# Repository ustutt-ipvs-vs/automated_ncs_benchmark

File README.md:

# Automated NCS Benchmark Setup
This repository contains the source code, hardware schematics, 3D printing files, and documentation of the open source benchmark setup described in the paper "Combining Dynamic Deterministic Latency Bounds and Networked Control Systems".

The paper can be found here: https://doi.org/10.1109/IPCCC59868.2024.10850021

The video below shows a demo of an automated evaluation with 15 configurations and re-swing-ups between each configuration.

[Demo Video](https://github.com/ustutt-ipvs-vs/automated_ncs_benchmark/assets/69897594/da2cac4a-8f67-4f81-817d-bd36dadb8c46)

## Overview
This repository is structured as follows:

- `sender-receiver-linux`: Software components for the sender side and receiver side computers
- `sender-receiver-teensy`: Sender and receiver scripts for the Teensy microcontrollers
- `network-config`: Bash scripts to configure the software switch and the endpoints
    - `scheduling-switch-config`: Scripts to configure the Qdisc and queue sizes at the software switch
- `control-approaches-design`: Files containing calculations for the parameters of the various control approaches for the inverted pendulum.
- `PCB-Design`: Design files of the sender and receiver PCB (KiCad)
- `3d-printable-parts`: Design files of the 3D-printed parts that were used for the construction of the inverted pendulum.
- `photos`: Photos of the inverted pendulum

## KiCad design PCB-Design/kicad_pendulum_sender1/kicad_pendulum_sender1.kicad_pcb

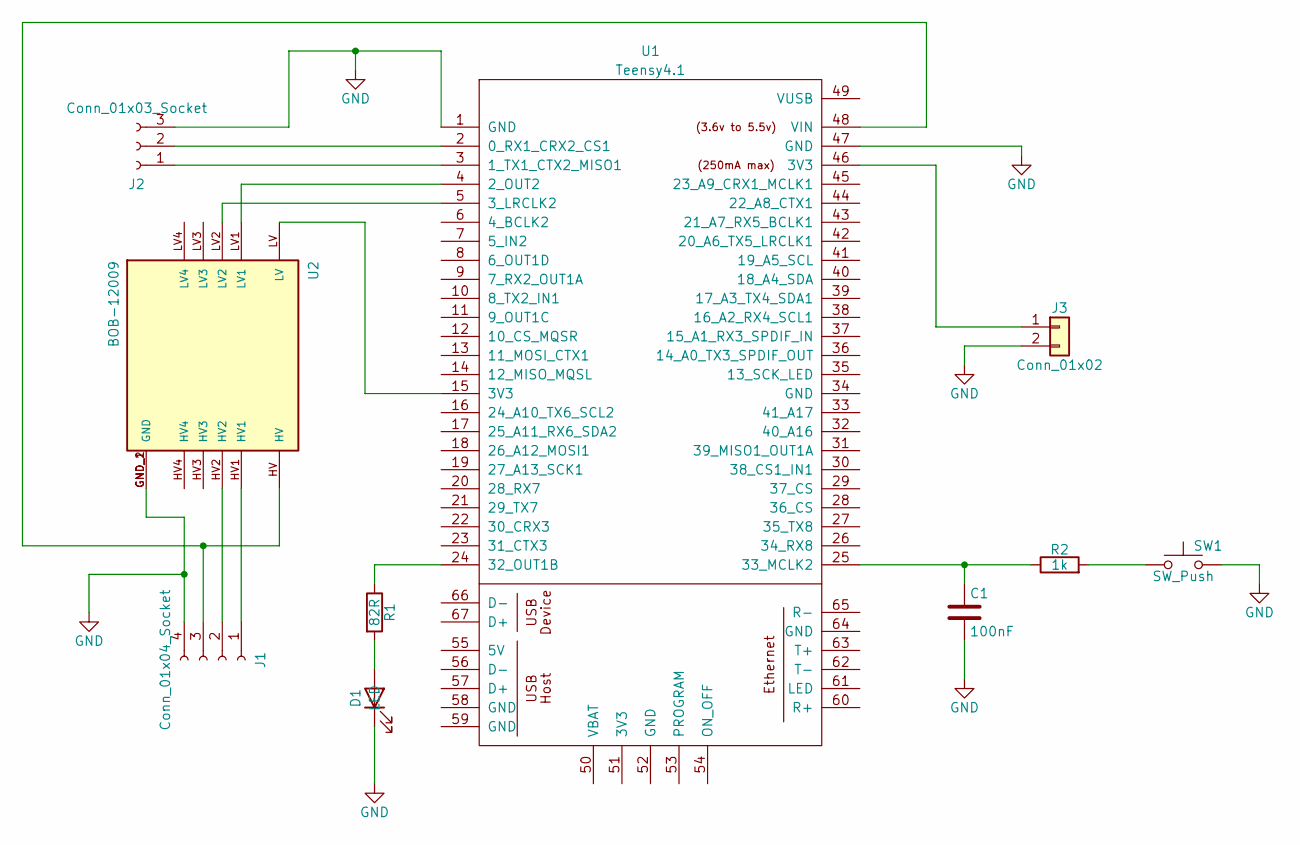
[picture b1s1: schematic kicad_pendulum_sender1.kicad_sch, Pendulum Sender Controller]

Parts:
C1: 100nF; C_Disc_D4.7mm_W2.5mm_P5.00mm
D1: LED; LED_D3.0mm
J1: Conn_01x04_Socket; TerminalBlock_bornier-4_P5.08mm
J2: Conn_01x03_Socket; TerminalBlock_bornier-3_P5.08mm
J3: Conn_01x02; TerminalBlock_bornier-2_P5.08mm
R1: 82R; R_Axial_DIN0207_L6.3mm_D2.5mm_P10.16mm_Horizontal
R2: 1k; R_Axial_DIN0207_L6.3mm_D2.5mm_P10.16mm_Horizontal
SW1: SW_Push; SW_PUSH_6mm_H5mm
U1: Teensy4.1; Teensy41
U2: BOB-12009; CONV_BOB-12009; PARTREV 01

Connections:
GND: C1.2, D1.1 (K), J1.4, J2.3, J3.2, SW1.2, U1.1 (GND), U1.47 (GND), U2.GND_1 (GND), U2.GND_2 (GND)
unnamed: D1.2 (A), R1.2
unnamed: J1.1, U2.HV1
unnamed: J1.2, U2.HV2
unnamed: J1.3, U1.48 (VIN), U2.HV
unnamed: J2.1, U1.3 (1_TX1_CTX2_MISO1)
unnamed: J2.2, U1.2 (0_RX1_CRX2_CS1)
unnamed: J3.1, U1.46 (3V3)
unnamed: R2.2, SW1.1
unnamed: U1.4 (2_OUT2), U2.LV1
unnamed: U1.15 (3V3), U2.LV
unnamed: U1.5 (3_LRCLK2), U2.LV2
unnamed: R1.1, U1.24 (32_OUT1B)
unnamed: C1.1, R2.1, U1.25 (33_MCLK2)

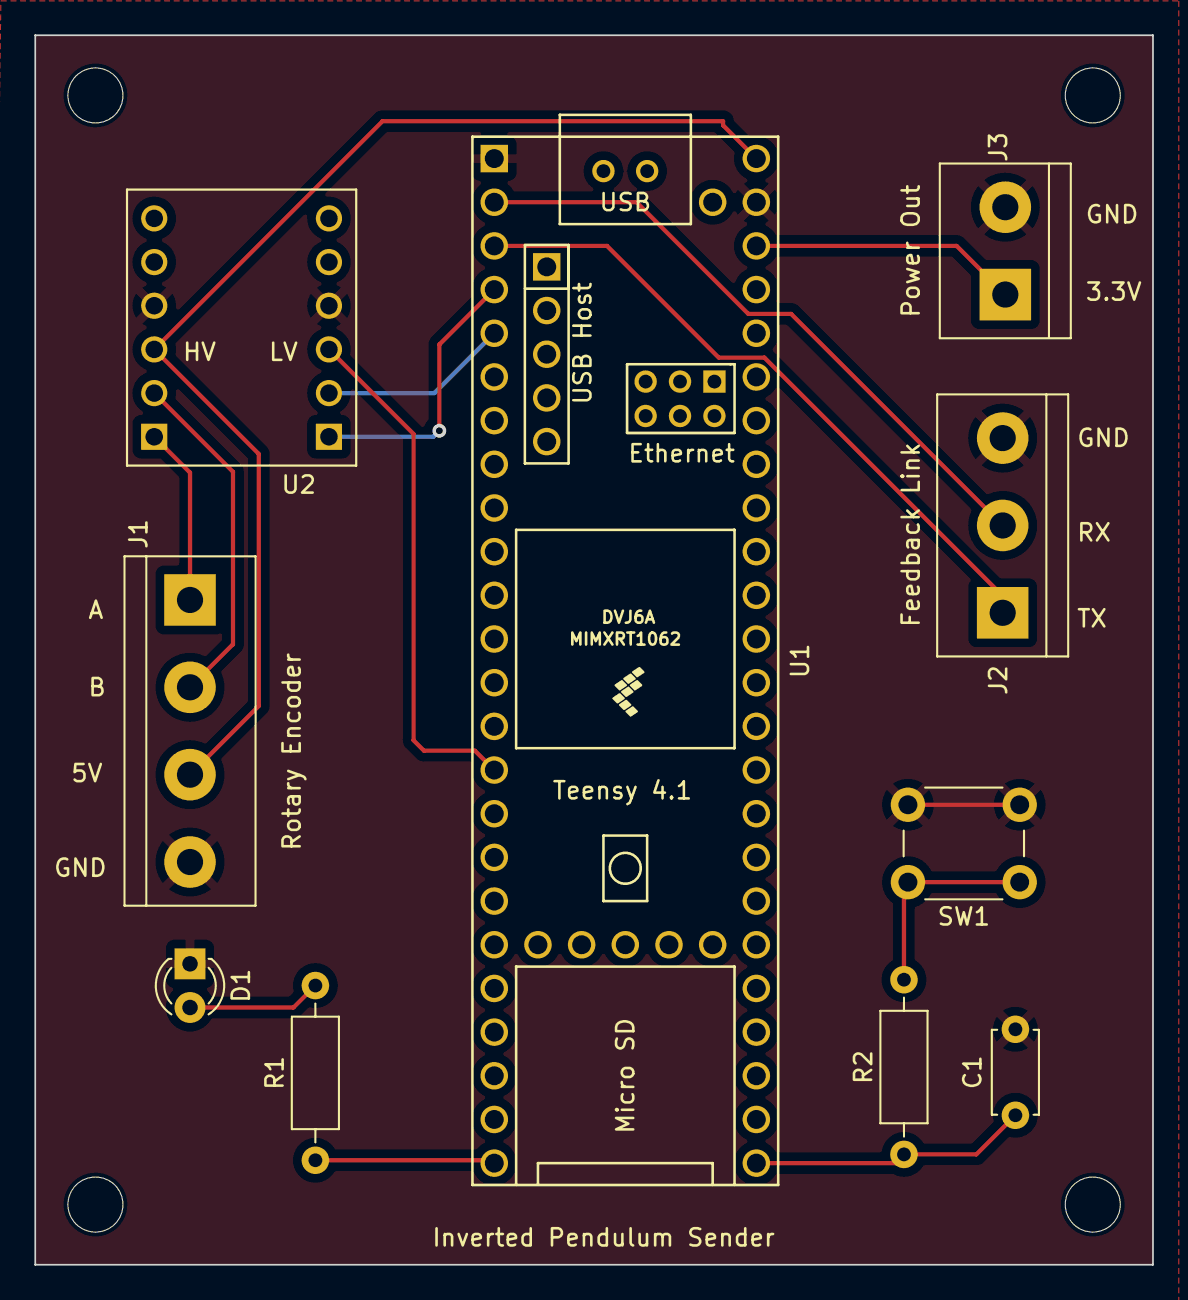
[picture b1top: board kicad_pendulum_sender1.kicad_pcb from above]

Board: 2 copper layers, 65.0 x 71.5 mm, 10 parts (0 on the bottom side), 14 nets.

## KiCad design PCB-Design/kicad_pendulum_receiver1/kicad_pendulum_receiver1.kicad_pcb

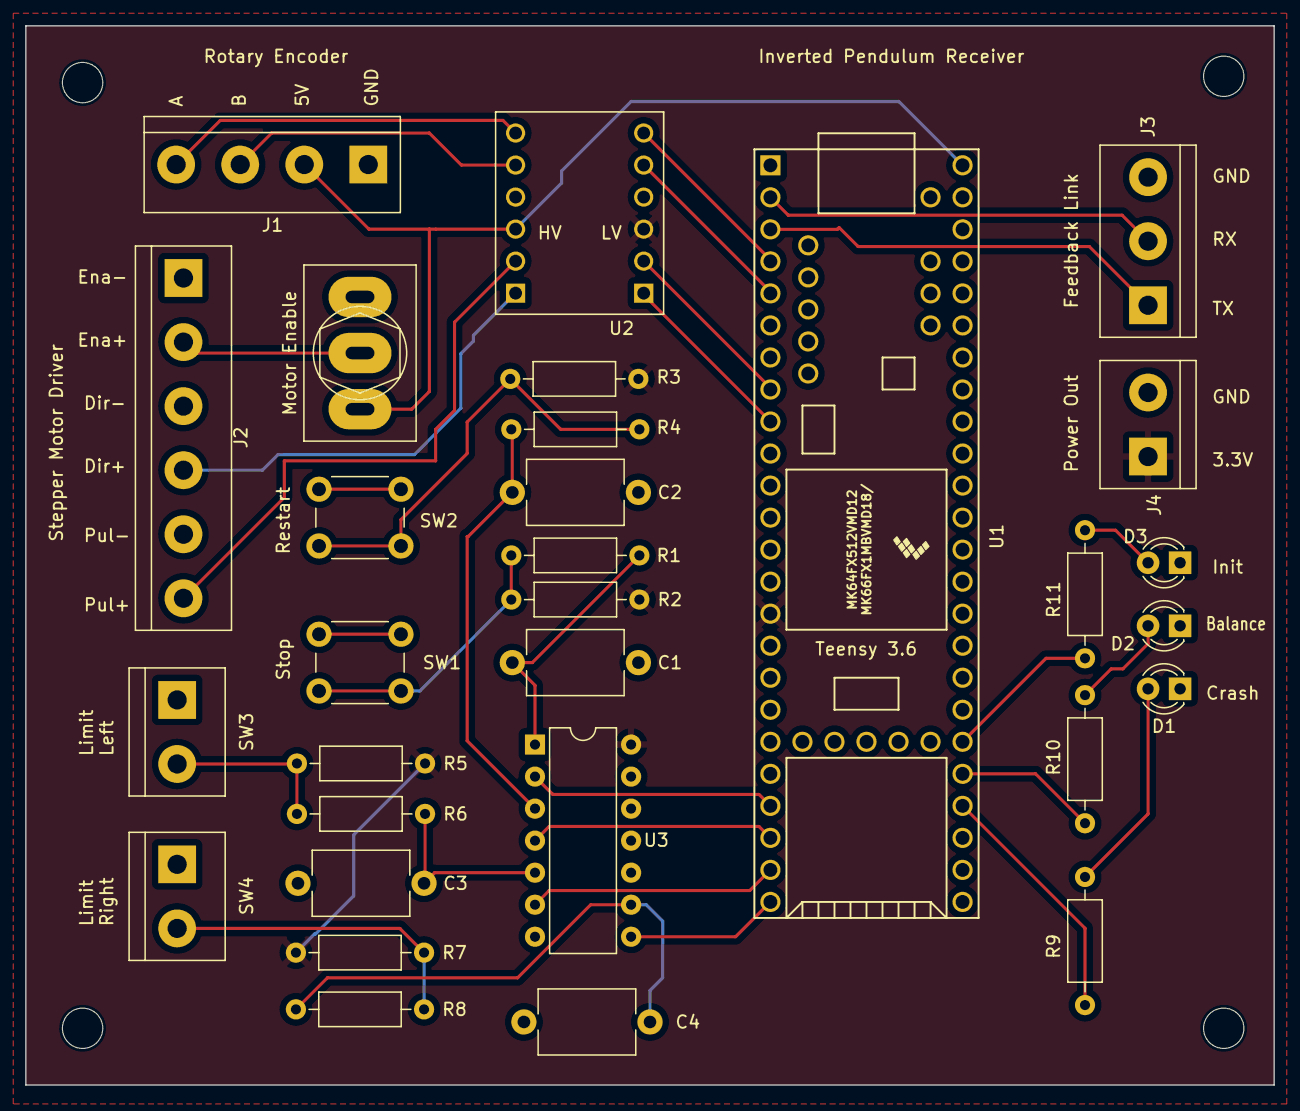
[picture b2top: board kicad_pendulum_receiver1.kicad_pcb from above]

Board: 2 copper layers, 99.0 x 84.0 mm, 30 parts (0 on the bottom side), 32 nets.

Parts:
C1, C2, C3, C4: 100nF; C_Disc_D7.5mm_W5.0mm_P10.00mm
D1, D2, D3: LED; LED_D3.0mm
J1: Screw_Terminal_01x04 Enc; TerminalBlock_bornier-4_P5.08mm
J2: Screw_Terminal_01x06 Motor; TerminalBlock_bornier-6_P5.08mm
J3: Screw_Terminal_01x03; TerminalBlock_bornier-3_P5.08mm
J4: Screw_Terminal_01x02; TerminalBlock_bornier-2_P5.08mm
R1, R4, R6, R8: 1k; R_Axial_DIN0207_L6.3mm_D2.5mm_P10.16mm_Horizontal
R2, R3, R5, R7: 10k; R_Axial_DIN0207_L6.3mm_D2.5mm_P10.16mm_Horizontal
R9, R10, R11: 82R; R_Axial_DIN0207_L6.3mm_D2.5mm_P10.16mm_Horizontal
SW1, SW2: SW_Push; SW_PUSH_6mm_H5mm
SW3, SW4: SW_Push; TerminalBlock_bornier-2_P5.08mm
SW5: SW_DPDT_x2; SW_Toggle_Blue_wSlots
U1: Teensy3.6; Teensy35_36
U2: BOB-12009; CONV_BOB-12009
U3: 74HC14; DIP-14_W7.62mm

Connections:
GND: C1.2, C2.2, C3.2, C4.2, D1.1 (K), D2.1 (K), D3.1 (K), J1.1, J2.1, J2.3, J2.5, J3.3, J4.2, SW1.1, SW2.1, SW3.1, SW4.1, SW5.3 (C), U1.1 (GND), U2.GND_1 (GND), U2.GND_2 (GND), U3.7 (GND)
unnamed: C1.1, R1.2, U3.1
unnamed: C2.1, R4.2, U3.3
unnamed: C3.1, R6.2, U3.5
unnamed: C4.1, R8.2, U3.9
unnamed: D1.2 (A), R9.1
unnamed: D2.2 (A), R10.1
unnamed: D3.2 (A), R11.1
unnamed: J1.2, SW5.1 (A), U1.53 (VIN), U2.HV
unnamed: J1.3, U2.HV3
unnamed: J1.4, U2.HV4
unnamed: J2.2, SW5.2 (B)
unnamed: J2.4, U2.HV1
unnamed: J2.6, U2.HV2
unnamed: J3.1, U1.3 (1_TX1_MISO1_TOUCH)
unnamed: J3.2, U1.2 (0_RX1_MOSI1_TOUCH)
unnamed: R1.1, R2.2, SW1.2
unnamed: R3.2, R4.1, SW2.2
unnamed: R5.2, R6.1, SW3.2
unnamed: R7.2, R8.1, SW4.2
unnamed: U1.4 (2_PWM), U2.LV4
unnamed: U1.5 (3_PWM_CAN0TX_SCL2), U2.LV3
unnamed: U1.8 (6_PWM), U2.LV2
unnamed: U1.9 (7_RX3_MISO0_SCL0), U2.LV1
unnamed: U1.21 (29_PWM_CAN0TX_TOUCH), U3.2
unnamed: U1.22 (30_PWM_CAN0RX_TOUCH), U3.4
unnamed: U1.23 (31_A12_RX4_CS1), U3.6
unnamed: U1.24 (32_A13_TX4_SCK1), U3.8
unnamed: R9.2, U1.33 (36_A17_PWM)
unnamed: R10.2, U1.34 (37_A18_PWM_SCL1)
unnamed: R11.2, U1.35 (38_A19_PWM_SDA1)
VCC: J4.1, R2.1, R3.1, R5.1, R7.1, U1.15 (3.3V), U2.LV, U3.14 (VCC)

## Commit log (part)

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2022-10-17 Teensy code for Serial via USB approach
2022-10-17 Python code for local serial via USB
2022-10-22 Serial Sensor to Actuator in C++
    Is a bit faster than the Python implementation
2022-10-22 Arduino: Remove balance timer; immediately act when new value received
    Delay between samples is now fully controlled by the sender side.
2022-10-24 Raspi UDP sender / receiver scripts
2022-11-30 Started to implement token bucket
2022-12-02 Token Bucket as CLion Project
2022-12-21 Config scripts for network with VLANs
2023-01-02 Change interface for custom scheduling in setup scripts
2023-01-04 Implement Multi-threaded Cross Traffic Senders with Logging
2023-01-10 Bugfix: Report packet sent to TokenBucket
2023-01-11 Use pointer for TokenBucket to make use of polymorphism
    This way the static type (TokenBucket) can differ from the dynamic type.
2023-01-11 Sender side for pendulum
2023-01-11 Restructured Logging to make Scheduling Information dynamic
    Before the change all logging classes expected the use of a TokenBucket.
    However, as different scheduling algorithms are to be evaluated, it is
    important that this can be swapped for another scheduling algorithm.
2023-01-11 Add Pendulum Receiver Side
2023-01-11 Instantiate PendulumSender and PendulumReceiver in main()
    When instantiated at variable creation (i.e. before main), this led to issues with the CppLinuxSerial library. It complained about the device file not being open.
2023-01-11 CLion Project: Remove unnecessary files
2023-01-12 Fix parsing of pendulum sensor payload in logger
    The samplingPeriodMillis attribute was not parsed from the string correctly.
2023-01-19 PendulumReceiver: Save log to file on stop
2023-01-19 Add logging off actuator information
2023-01-19 Arduino Receivers: More machine-readable logging format
    Semicolon-separated values are easier to parse automatically.
2023-01-19 Use unsigned long long to store unix timestamp millis
    Before long was used which caused an overflow on Raspberry Pi 4.
    long is ambiguously defined as 'at least 4 bytes'. Implementation is system-dependent.
    unsigned long long is defined to always have 8 bytes.
2023-01-24 More generic PriorityDeterminer instead of TokenBucket
    This enables swapping out the scheduling mechanism easily.
2023-01-25 Extend Linux Receiver to send pause signals to Teensy
    These signals will pause the pendulum for a given amount of milliseconds to
    cause disruption. This decreases the stability of the pendulum which makes the
    tests harder.
2023-01-25 Update CMake config
2023-01-27 Linux C++: Add support for sender feedback logging
2023-01-27 Remove a debug print
2023-01-28 Add PriorityDeterminer.cpp to CMakeLists.txt
2023-01-28 Scheduling config scripts: Call included script with relative path
    This way you can also call the script from any other directory.
2023-01-29 PriorityDeterminer: Add reset function
2023-01-29 Add MultiPriorityTokenBucket priority determiner
2023-01-29 CrossTrafficSenderOrchestrator: Change default initialization
2023-02-02 MPTB: Limit best priority by initial priority
2023-02-02 pendulum_receiver1.ino: Parameters for more sampling periods
2023-02-02 Pendulum Sender: Predefined parameters selections via CL arguments
2023-02-02 pendulum_sender1.ino: Restructure sampling period determination
    Now the sampling period is determined by the maximum change between the
    current encoder value and the last 100 encoder values (last second).
    Besides this, the sensor is checked every 10ms regardless of the
    sample transmission period. Thus, the sensor can react faster to
    changes.
2023-02-03 Pad payloads to 32 bytes
    This way the payload has a constant size which makes calculations more precise.
    Additionally: If multiple payloads are received via Serial, they get split up and sent in different UDP packets.
2023-02-03 MPTB: Change calculations of costs and thresholds
2023-02-07 Use priority 0 data rate as bucket r
    This way it is ensured that the sender stays in priority 0 when it sends with data rate r
2023-02-08 Arduino receiver: Parameters for more sampling periods
    These were generated using Ben Carabelli's Julia Script
2023-03-12 Switch config for real cross traffic
2023-03-12 Notice how to run program with root privileges (shared libs)
2023-03-18 Commit some files that were still uncommitted for ages
2023-03-19 Update graphic for network topology
2023-03-19 Typo
2023-03-19 Add readme for sender-receiver-linux
2023-03-19 Extend readme
2023-09-07 Modifications to PendulumSender before fork
2023-09-14 Linux Sender: Enforce unified sampling period
2023-09-30 Add prioMapping to MultiPriorityTokenBucket class
    I found this code change on the switch PC. Probably it was created by
    Robin.
2023-09-30 configure-pen1-sender.sh: Change interface name
    Interface name now fits the interface of the thinkpad laptop (instead of ODROID).
2023-10-01 Clear serial buffer string before next read.
    This is required due to a change in the CppLinuxSerial library from
    February 2023:
    https://github.com/gbmhunter/CppLinuxSerial/pull/35
    Now, the SerialPort::Read method doesn't overwrite the buffer string
    anymore but appends new input to it.
2023-10-02 Create default prioMapping in constructor without prioMapping parameter
2023-10-02 exampleSenderConfig.json
2023-10-02 Transmit history size and sampling periods to sender teensy on initialization
2023-10-02 Teensy Sender: Receive init values from serial
2023-10-04 SenderConfig.h: Improve order in code
2023-10-04 Create ReceiverConfig class
2023-10-04 example receiver config file
2023-10-04 PendulumSender.cpp: Add buffer clear instruction
2023-10-04 PendulumReceiver.cpp: Clear buffer before read, not after
2023-10-10 Fix network interface names in configure-switch.sh
2023-10-11 Missing code changes of TokenBucketInfoEntry and MultiPriorityTokenBucket
2023-10-11 Fix MPTB file changes before config file mode
2023-10-11 Change numPriorities to numThresholds
2023-10-13 Sender Config added
2023-10-20 Create SenderMultiConfig class and MPTBSubConfig class
2023-10-20 PendulumSenderMain: code to start MPTB sequence
2023-10-20 Add exampleSenderConfig.json
2023-10-20 PendulumSender sendNewMptbConfigSignal method
2023-10-23 PendulumSender: Function to send end signal
2023-10-23 PendulumSenderMain: Send new config and end signals
2023-10-23 exampleSenderSequenceConfig.json: Change durations
2023-10-25 MultiPriorityTokenBucket: Initialize currentSeverityLevel in constructor
    Also added a bounds check in getCostOfCurrentPriority() since there was a segfault that was hard to debug.
2023-10-25 Use vec.at(index) instead of vec[index] when accesing vectors to enforce bounds checking
    Bounds checking prevents segmentation faults which are hard to debug.
2023-10-27 PendulumSenderMain.cpp Use .at(index) instead of [index]
2023-10-27 Store Logger as pointer to allow swap without delete
    This is required so that the logger object can be replaced in the PendulumSender and PendulumReceiver while the old logger object is still in progress of saving to file.
2023-10-27 Logger.cpp Delete object only once on save
    Object was deleted multiple times which caused a segmentation fault.
2023-10-27 exampleSenderSequenceConfig.json: Remove initialPriorityClass attribute
    This attribute is unnecessary and was only included due to a copy-paste error
2023-10-30 Sender config: Add bias parameter
2023-10-30 PendulumSenderMain.cpp: Pass angle bias to PendulumSender
2023-10-30 config file examples: Add bias attribute
2023-10-30 Create a Readme for pendulum characteristics analysis
2023-11-01 analyze_trace.py: Restructure code, add calculation of damping coefficient
2023-11-06 Teensy Receiver logging every packet, cleaning measurement Python code
2023-11-06 pendulum_sender1.ino: Fix Feedback serial packet receiving
    For some reason the feedback packets caused high delays in the sender when used with Teensy 4.1.
    The problem turned out to be the
    FeedbackSerial.readStringUntil(':')
    which blocks the execution until a ':' is found.
    This was now fixed by using non-blocking FeedbackSerial.read() calls.
2023-11-10 Receiver swing-up prototype code
2023-11-13 Receiver linux: Support for swing-up signals
2023-11-15 Print swingUpBehavior config value as string
2023-11-15 exampleReceiverConfig.json: Add swingUpBehavior
2023-11-17 Receiver teensy: Reset control parameters at new config
2023-11-17 Linux sender/receiver: Reset state on "grace period ended" signal
2023-11-17 Pendulum receiver linux: Search for grace period end signal more generally
    As the buffer might fill during grace period (due to network socket blocking the program execution), we need to search the whole serial buffer for the signal and not just the start of it.
2023-11-17 Teensy sender/receiver: Send grace period end signals
2023-11-17 Teensy receiver: Use resetControlParameters() method
2023-11-17 Teensy receiver: Do not send logs when using Feedback serial for encoder values
    To prevent buffer bloat
2023-11-17 rename pendulumSailType to sailType
2023-11-17 Add sailType to exampleReceiverConfig.json
2023-11-22 update new controller generation
2023-11-22 Readme file for matlab installation
2023-11-27 add Kalman Filter comments and update delay in neuerVersuch.m
2023-11-29 Kalman LQR docs: Fix LaTeX
    GitLab's LaTeX support seems a bit picky
2023-11-29 Receiver Teensy: Fix matrix dimensions
2023-11-30 uopdate kalman filter description
2023-12-01 Teensy: Transmit angular velocity from sender to receiver
2023-12-01 Teensy: Work on new Kalman filter and controller
2023-12-04 Remove debug print
2023-12-06 Adjust sail parameters for sail14
    The new 3D print is heavier, which gives the system more inertia
2023-12-06 Missing semicolon
2023-12-06 Change default R and Q0 diagonal values to 1
    Reason: Pendulum behaves absolutely strange when these values are set to 0.
2023-12-11 change sail to 17
2023-12-11 Linux sender: Parameters for sensitivity factor and offset
2023-12-11 Teensy sender: Use sensitivity parameters
2023-12-11 Teensy receiver: Configuration option for control approach
2023-12-11 4th control approach: Carabelli Kalman + IST controller
2023-12-15 MPTB sub-configs: Name field for log filenames
2023-12-15 Parse logfile name from end signal
2024-01-02 Results controller comparison, python script for controller comparison plots
2024-01-08 Matlab readme + updated controller parameters
2024-02-16 Julia script to generate Carabelli parameters for multiple sampling rates
2024-02-16 Integrate new Carabelli parameters header file into receiver teensy
2024-02-19 Re-generate CarabelliParameters.h with new Julia script
2024-02-19 Pendulum Sender: Add network delay to transmitted sampling period.
2024-02-23 Carabelli parameters up to 200ms delay instead of 80ms
2024-03-26 Writeup for LQR with delay
2024-03-26 Implement delay in LQR parameter calculation (in separate matlab script)
2024-04-09 PendulumSender.cpp: Include network delay in payload
2024-04-09 Julia Script: Add code to append A, B matrices to header file.
2024-04-09 Adapt Arduino code (sender, receiver) to handle latency.
2024-04-10 Receiver config files
2024-04-10 Teensy receiver: Explicitely stop motor before swing-up
2024-04-12 Teensy receiver: Tidy up code
2024-04-12 Receiver side: Remove pause feature and IST Kalman filter params
2024-04-12 Remove "created by ... on ..." comments from classes
2024-04-12 Remove cross traffic component
2024-04-12 Introduce "mLQR" and "RobustIO" instead of internal names.
2024-04-15 Remove pause config fields from receiver config files
2024-04-15 Remove logging time limit
2024-04-15 Weed out unused files from the parameter calculation project folder
2024-04-15 Add readme for Julia script
2024-04-15 Started to implement simpleThreshold approach in Teensy receiver
2024-04-17 Fix bugs in Teensy sender code
2024-04-17 Sender Linux: Add documentation for new triggering approach config option
2024-12-24 Teensy receiver: Remove non-required using statement
    In the new version of the BasicLinearAlgebra library, this is no longer necessary and even leads to compile errors.
2024-12-24 Readme: Specify commit hashes for used libraries
    The libraries may introduce breaking changes, so better fix them to a specific commit.
2024-12-24 Reorganize folders of repository
2025-01-08 Added 3d printable parts STL + SCAD
2025-01-15 Add directory descriptions to readme

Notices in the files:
PCB-Design/kicad_pendulum_receiver1/kicad_pendulum_receiver1.kicad_pcb:
(c) 2023 David Augustat
PCB-Design/kicad_pendulum_sender1/kicad_pendulum_sender1.kicad_pcb:
Inverted Pendulum Sender V1.0 (c) 2023 David Augustat
